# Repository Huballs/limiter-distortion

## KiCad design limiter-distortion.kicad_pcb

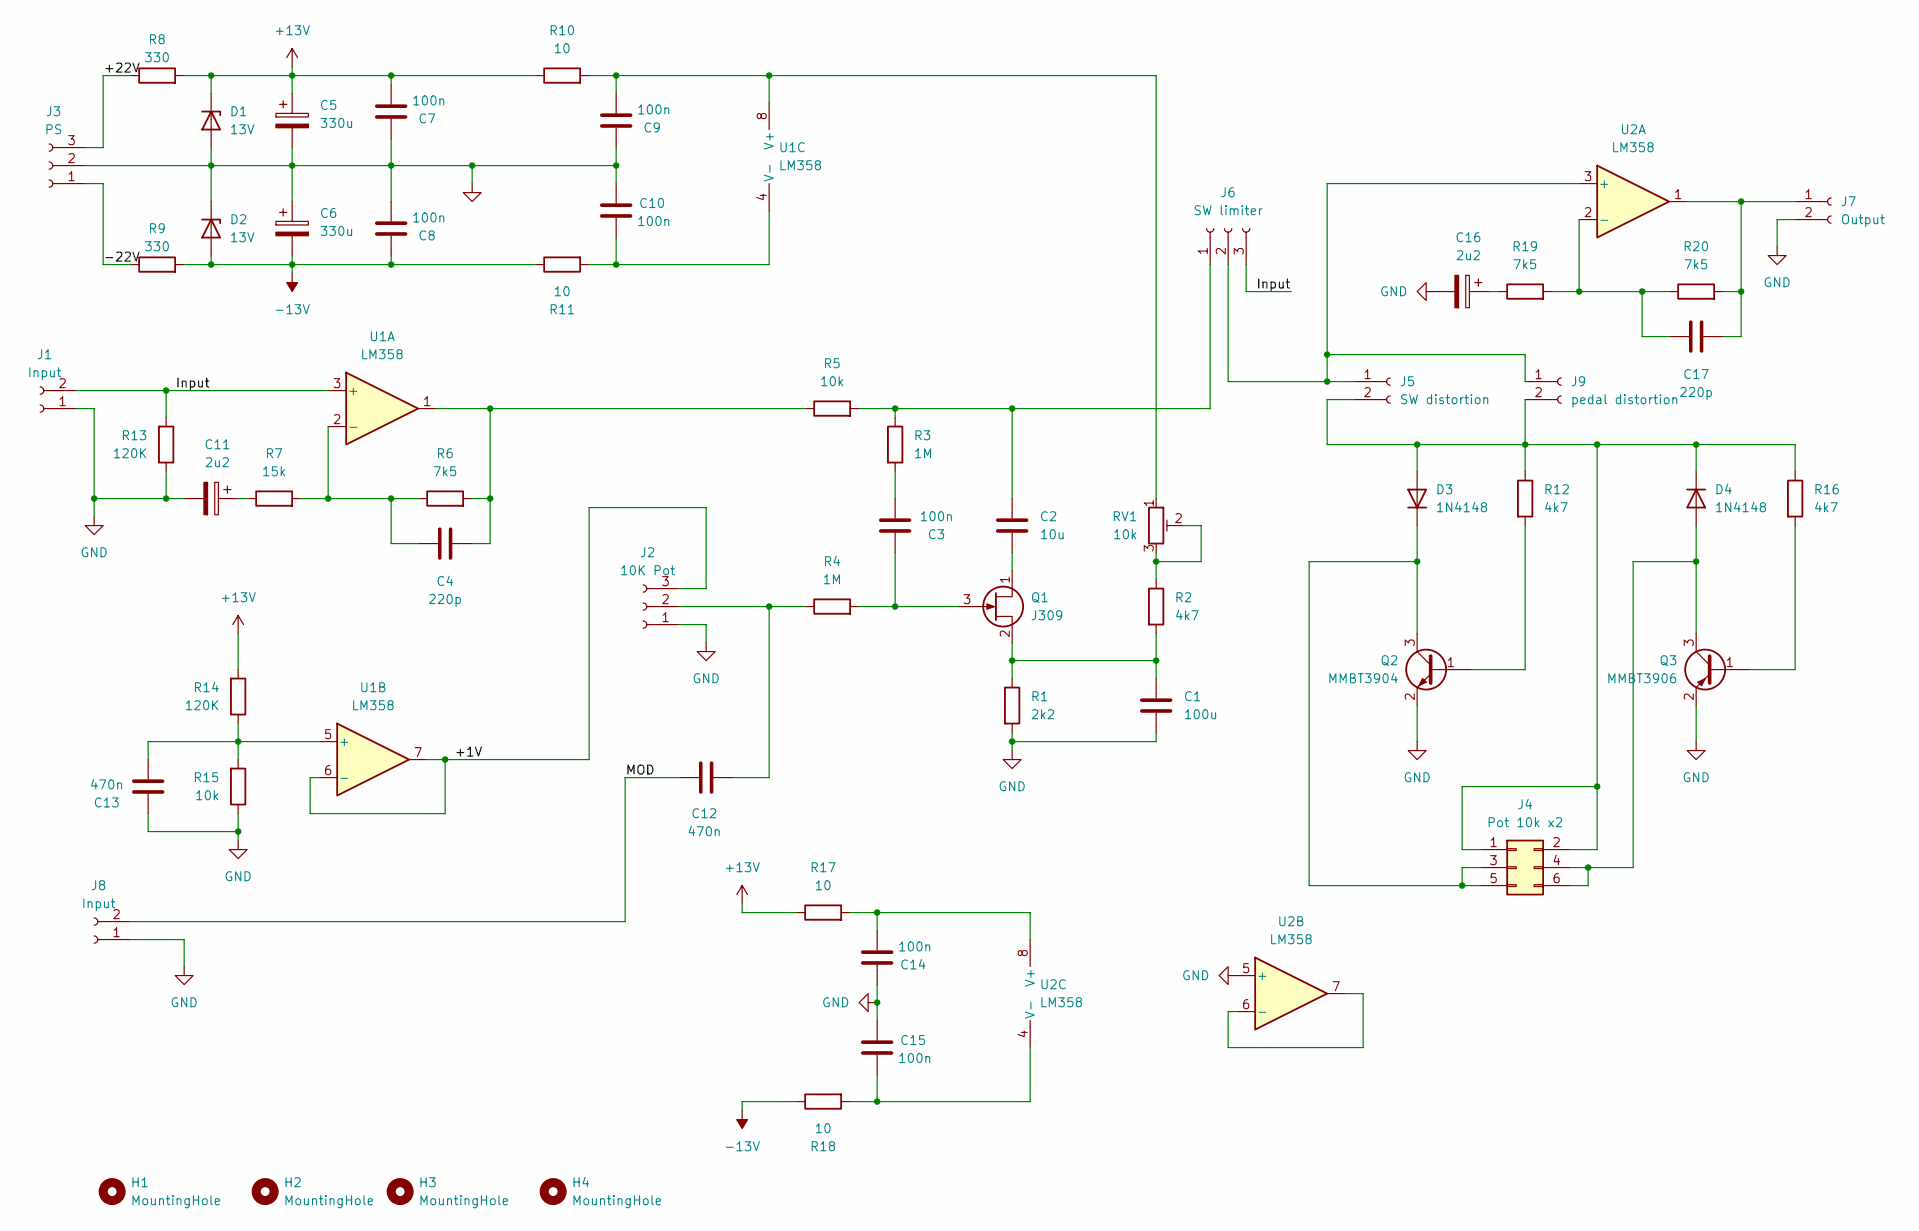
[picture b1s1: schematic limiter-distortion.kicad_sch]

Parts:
C1: 100u; C_Radial_D6.3mm_H5.0mm_P2.50mm
C2: 10u; C_Radial_D6.3mm_H5.0mm_P2.50mm
C3: 100n; C_Rect_L7.0mm_W2.5mm_P5.00mm
C4, C17: 220p; C_0805_2012Metric_Pad1.18x1.45mm_HandSolder
C5, C6: 330u; CP_Elec_10x10.5
C7, C8, C9, C10, C14, C15: 100n; C_0805_2012Metric_Pad1.18x1.45mm_HandSolder
C11, C16: 2u2; CP_Radial_D6.3mm_P2.50mm
C12, C13: 470n; C_Rect_L7.0mm_W2.5mm_P5.00mm
D1, D2: 13V; D_A-405_P12.70mm_Horizontal
D3, D4: 1N4148; D_DO-35_SOD27_P7.62mm_Horizontal
H1, H2, H3, H4: MountingHole; MountingHole_3.2mm_M3
J1, J8: Input; PinHeader_1x02_P2.54mm_Vertical
J2: 10K Pot; JST_EH_B3B-EH-A_1x03_P2.50mm_Vertical
J3: PS; JST_EH_B3B-EH-A_1x03_P2.50mm_Vertical
J4: Pot 10k x2; PinHeader_2x03_P2.54mm_Vertical
J5: SW distortion; PinHeader_1x02_P2.54mm_Vertical
J6: SW limiter; JST_EH_B3B-EH-A_1x03_P2.50mm_Vertical
J7: Output; PinHeader_1x02_P2.54mm_Vertical
J9: pedal distortion; PinHeader_1x02_P2.54mm_Vertical
Q1: J309; SOT-23
Q2: MMBT3904; SOT-23
Q3: MMBT3906; SOT-23
R1: 2k2; R_1206_3216Metric_Pad1.30x1.75mm_HandSolder
R2, R12, R16: 4k7; R_1206_3216Metric_Pad1.30x1.75mm_HandSolder
R3, R4: 1M; R_1206_3216Metric_Pad1.30x1.75mm_HandSolder
R5, R15: 10k; R_1206_3216Metric_Pad1.30x1.75mm_HandSolder
R6, R19, R20: 7k5; R_1206_3216Metric_Pad1.30x1.75mm_HandSolder
R7: 15k; R_1206_3216Metric_Pad1.30x1.75mm_HandSolder
R8, R9: 330; R_2512_6332Metric_Pad1.40x3.35mm_HandSolder
R10, R11, R17, R18: 10; R_1206_3216Metric_Pad1.30x1.75mm_HandSolder
R13, R14: 120K; R_1206_3216Metric_Pad1.30x1.75mm_HandSolder
RV1: 10k; Potentiometer_ACP_CA9-V10_Vertical_Hole
U1: LM358; SOIC-8_3.9x4.9mm_P1.27mm
U2: LM358; SO-8_3.9x4.9mm_P1.27mm

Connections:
+13V: C5.1, C7.2, D1.1 (K), R8.2, R10.1, R14.2, R17.1
-13V: C6.2, C8.1, D2.2 (A), R9.2, R11.1, R18.1
/+1V: J2.3, U1.6 (-), U1.7
/+22V: J3.3, R8.1
/-22V: J3.1, R9.1
/Input: J1.2, J6.3, R13.2, U1.3 (+)
/MOD: C12.1, J8.2
GND: C1.2, C5.2, C6.1, C7.1, C8.2, C9.1, C10.1, C11.2, C13.1, C14.1, C15.1, C16.2, D1.2 (A), D2.1 (K), J1.1, J2.1, J3.2, J7.2, J8.1, Q2.2 (E), Q3.2 (E), R1.2, R13.1, R15.1, U2.5 (+)
unnamed: C3.1, R3.2
unnamed: C4.2, R5.1, R6.2, U1.1
unnamed: C11.1, R7.1
unnamed: C16.1, R19.1
unnamed: D3.2 (A), D4.1 (K), J4.1, J4.2, J5.2, J9.2, R12.1, R16.1
unnamed: D3.1 (K), J4.3, J4.5, Q2.3 (C)
unnamed: D4.2 (A), J4.4, J4.6, Q3.3 (C)
unnamed: C12.2, J2.2, R4.1
unnamed: J5.1, J6.2, J9.1, U2.3 (+)
unnamed: C2.1, J6.1, R3.1, R5.2
unnamed: C17.2, J7.1, R20.2, U2.1
unnamed: C2.2, Q1.1 (D)
unnamed: C3.2, Q1.3 (G), R4.2
unnamed: C1.1, Q1.2 (S), R1.1, R2.2
unnamed: Q2.1 (B), R12.2
unnamed: Q3.1 (B), R16.2
unnamed: R2.1, RV1.2, RV1.3
unnamed: C4.1, R6.1, R7.2, U1.2 (-)
unnamed: C13.2, R14.1, R15.2, U1.5 (+)
unnamed: C9.2, R10.2, RV1.1, U1.8 (V+)
unnamed: C10.2, R11.2, U1.4 (V-)
unnamed: C17.1, R19.2, R20.1, U2.2 (-)
unnamed: U2.6 (-), U2.7
unnamed: C14.2, R17.2, U2.8 (V+)
unnamed: C15.2, R18.2, U2.4 (V-)

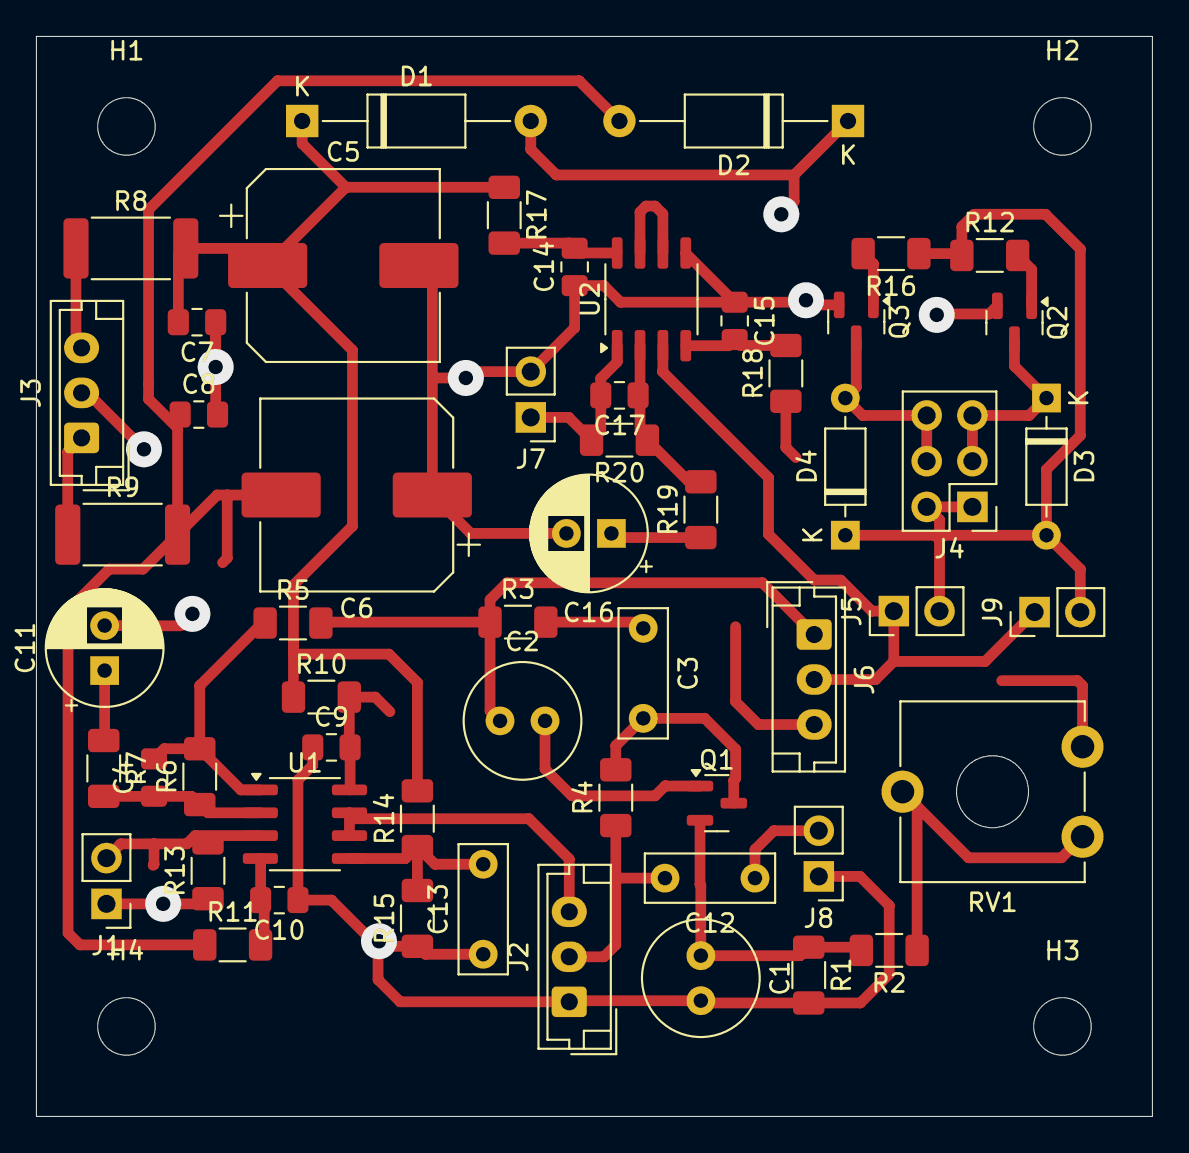
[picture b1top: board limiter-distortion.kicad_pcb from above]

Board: 2 copper layers, 62.0 x 60.0 mm, 60 parts (0 on the bottom side), 33 nets.

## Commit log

2025-04-20 done
